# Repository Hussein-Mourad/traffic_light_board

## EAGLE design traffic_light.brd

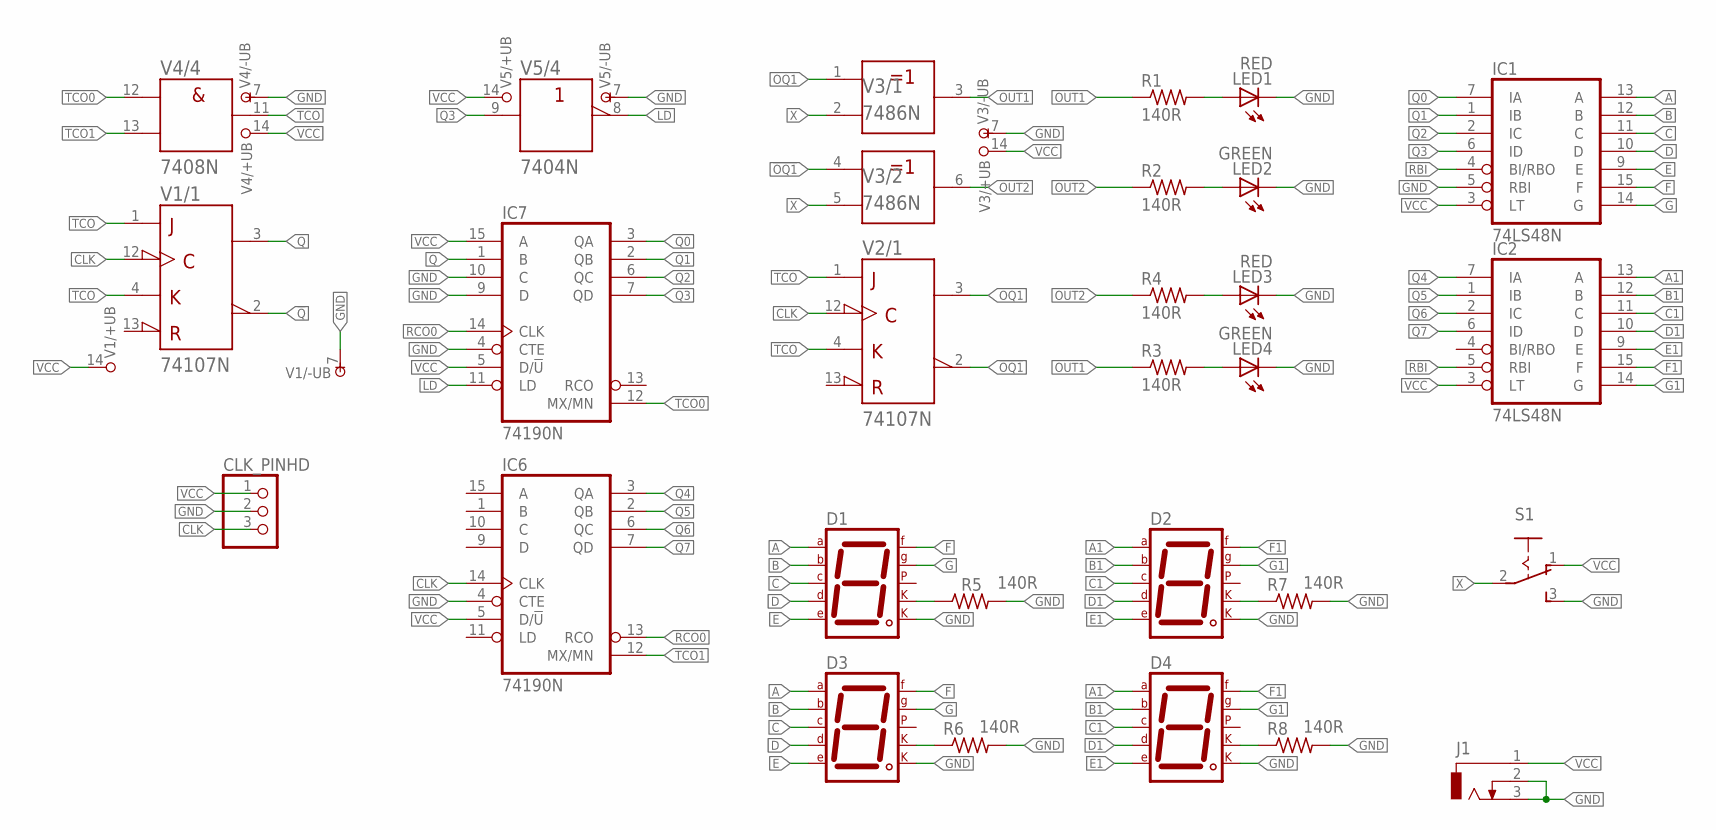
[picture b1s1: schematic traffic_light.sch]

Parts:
CLK_PINHD: PINHD-1X3; 1X03
D1, D2, D3, D4: 7SEG-CK; 7SEG-13
IC1, IC2: 74LS48N; DIL16
IC6, IC7: 74190N; DIL16
J1: CON_JACK; DCJ0303
LED1, LED3: RED; LED5MM
LED2, LED4: GREEN; LED5MM
R1, R2, R3, R4, R5, R6, R7, R8: 140R; 0204/7
S1: 255SB
V1, V2: 74107N; DIL14
V3: 7486N; DIL14
V4: 7408N; DIL14
V5: 7404N; DIL14

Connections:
!OQ1: V2.2 (!Q), V3.4 (A)
!Q: V1.2 (!Q)
+UB: V2.14 (+UB)
-UB: V2.7 (-UB)
A: D1.7 (A), D3.7 (A), IC1.13 (A)
A1: D2.7 (A), D4.7 (A), IC2.13 (A)
B: D1.6 (B), D3.6 (B), IC1.12 (B)
B1: D2.6 (B), D4.6 (B), IC2.12 (B)
C: D1.4 (C), D3.4 (C), IC1.11 (C)
C1: D2.4 (C), D4.4 (C), IC2.11 (C)
CLK: CLK_PINHD.3, IC6.14 (CLK), V1.12 (CLK), V2.12 (CLK)
D: D1.2 (D), D3.2 (D), IC1.10 (D)
D1: D2.2 (D), D4.2 (D), IC2.10 (D)
E: D1.1 (E), D3.1 (E), IC1.9 (E)
E1: D2.1 (E), D4.1 (E), IC2.9 (E)
F: D1.9 (F), D3.9 (F), IC1.15 (F)
F1: D2.9 (F), D4.9 (F), IC2.15 (F)
G: D1.10 (G), D3.10 (G), IC1.14 (G)
G1: D2.10 (G), D4.10 (G), IC2.14 (G)
GND: CLK_PINHD.2, D1.8 (CK2), D2.8 (CK2), D3.8 (CK2), D4.8 (CK2), IC1.5 (RBI), IC1.8 (GND), IC2.8 (GND), IC6.4 (CTE), IC6.8 (GND), IC7.4 (CTE), IC7.8 (GND), IC7.9 (D), IC7.10 (C), J1.2, J1.3, LED1.K (C), LED2.K (C), LED3.K (C), LED4.K (C), R5.2, R6.2, R7.2, R8.2, S1.3 (S), V1.7 (-UB), V3.7 (-UB), V4.7 (-UB), V5.7 (-UB)
LD: IC7.11 (LD), V5.8 (Y)
unnamed: D1.3 (CK1), R5.1
unnamed: D2.3 (CK1), R7.1
unnamed: D3.3 (CK1), R6.1
unnamed: D4.3 (CK1), R8.1
unnamed: LED1.A, R1.2
unnamed: LED2.A, R2.2
unnamed: LED3.A, R4.2
unnamed: LED4.A, R3.2
OQ1: V2.3 (Q), V3.1 (A)
OUT1: R1.1, R3.1, V3.3 (Y)
OUT2: R2.1, R4.1, V3.6 (Y)
Q: IC7.1 (B), V1.3 (Q)
Q0: IC1.7 (IA), IC7.3 (QA)
Q1: IC1.1 (IB), IC7.2 (QB)
Q2: IC1.2 (IC), IC7.6 (QC)
Q3: IC1.6 (ID), IC7.7 (QD), V5.9 (A)
Q4: IC2.7 (IA), IC6.3 (QA)
Q5: IC2.1 (IB), IC6.2 (QB)
Q6: IC2.2 (IC), IC6.6 (QC)
Q7: IC2.6 (ID), IC6.7 (QD)
RBI: IC1.4 (BI/RBO), IC2.5 (RBI)
RCO0: IC6.13 (RCO), IC7.14 (CLK)
TCO: V1.1 (J), V1.4 (K), V2.1 (J), V2.4 (K), V4.11 (Y)
TCO0: IC7.12 (MX/MN), V4.12 (A)
TCO1: IC6.12 (MX/MN), V4.13 (B)
VCC: CLK_PINHD.1, IC1.3 (LT), IC1.16 (VCC), IC2.3 (LT), IC2.16 (VCC), IC6.5 (D/!U), IC6.16 (VCC), IC7.5 (D/!U), IC7.15 (A), IC7.16 (VCC), J1.1, S1.1 (O), V1.14 (+UB), V3.14 (+UB), V4.14 (+UB), V5.14 (+UB)
X: S1.2, V3.2 (B), V3.5 (B)

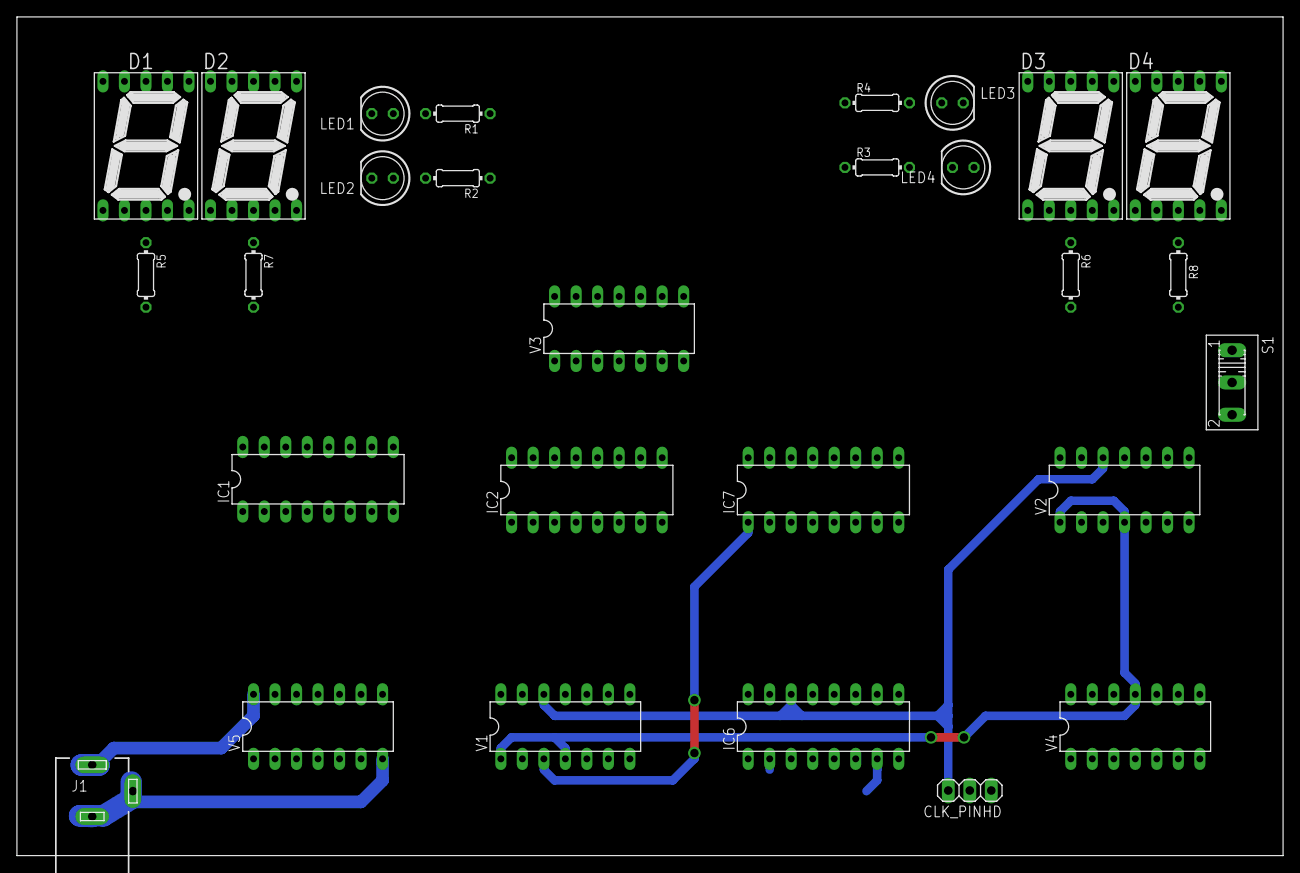
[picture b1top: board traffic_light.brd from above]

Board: 2 copper layers, 149.5 x 99.0 mm, 28 parts (0 on the bottom side), 45 nets.

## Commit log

2021-12-28 init
2021-12-28 schematics
2021-12-29 working on board
2021-12-29 sch tweaks
2021-12-31 board
2022-01-02 backup
